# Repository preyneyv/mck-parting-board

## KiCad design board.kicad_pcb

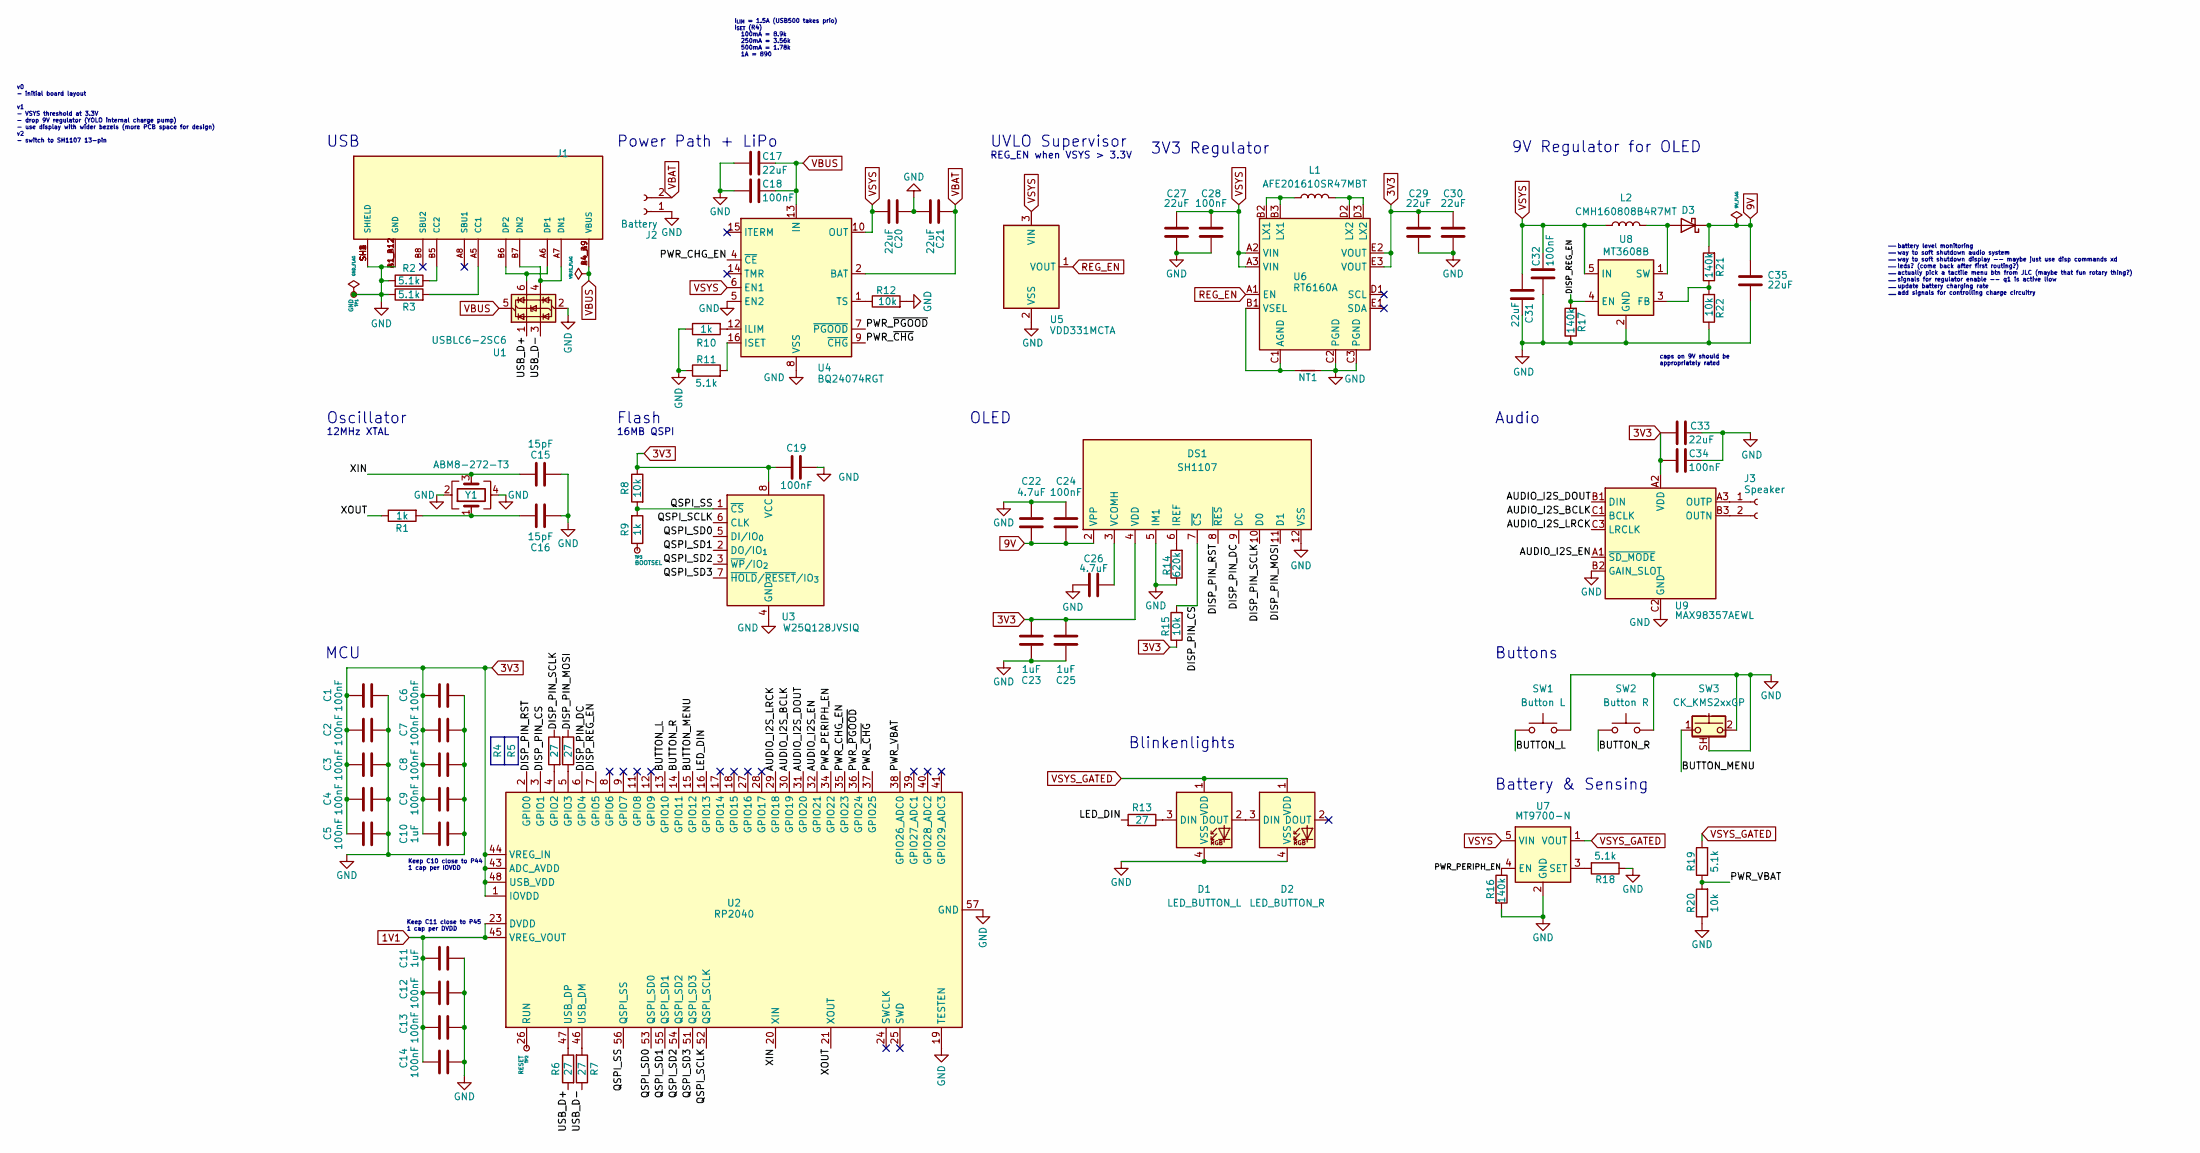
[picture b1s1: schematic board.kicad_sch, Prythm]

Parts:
C1, C2, C3, C4, C5, C6, C7, C8, C9, C12, C13, C14, C18, C19, C24, C28, C32, C34: 100nF; C_0201_0603Metric; LCSC C307380
C10, C11, C23, C25: 1uF; C_0201_0603Metric; LCSC C307385
C15, C16: 15pF; C_0201_0603Metric; LCSC C237567
C17, C20, C21, C27, C29, C30, C31, C33, C35: 22uF; C_0603_1608Metric; LCSC C2762594
C22, C26: 4.7uF; C_0402_1005Metric; LCSC C318563
D1: LED_BUTTON_L; LED_MX_6028R; LCSC C5242955
D2: LED_BUTTON_R; LED_MX_6028R; LCSC C5242955
D3: BAT20JFILM; D_SOD-323; LCSC C155590
DS1: SH1107; OLED_SH1107_13P
J1: UJ20-C-H-G-MSMT-6-P16-TR; SAMESKY_UJ20-C-H-G-MSMT-6-P16-TR; PARTREV 1.0; DigiKey 2223-UJ20-C-H-G-MSMT-6-P16-TRCT-ND
J2: Battery; JST_PH_B2B-PH-K_1x02_P2.00mm_Vertical; DigiKey 455-1704-ND
J3: Speaker; JST_ZH_B2B-ZR_1x02_P1.50mm_Vertical; DigiKey 455-B2B-ZR-ND
L1: AFE201610SR47MBT; L_Murata_DFE201610P; LCSC C22459313
L2: CMH160808B4R7MT; L_0603_1608Metric; LCSC C394952
NT1: NetTie_2; NetTie-2_SMD_Pad0.5mm
R1, R9, R10: 1k; R_0201_0603Metric; LCSC C138165
R2, R3, R11, R18, R19: 5.1k; R_0201_0603Metric; LCSC C274341
R4, R5, R6, R7, R13: 27; R_0201_0603Metric; LCSC C273268
R8, R12, R15, R20, R22: 10k; R_0201_0603Metric; LCSC C138117
R14: 620k; R_0201_0603Metric; LCSC C295860
R16, R17, R21: 140k; R_0201_0603Metric; LCSC C138174
SW1: Button L; SW_Hotswap_Kailh_MX_Plated
SW2: Button R; SW_Hotswap_Kailh_MX_Plated
SW3: CK_KMS2xxGP; SW_SPST_CK_KMS2xxGP; DigiKey 401-1614-1-ND
TP1: GND; TestPoint_Pad_1.0x1.0mm
TP2: RESET; TestPoint_Pad_1.0x1.0mm
TP3: BOOTSEL; TestPoint_Pad_1.0x1.0mm
U1: USBLC6-2SC6; SOT-23-6; LCSC C7519
U2: RP2040; QFN-56-1EP_7x7mm_P0.4mm_EP3.2x3.2mm; LCSC C2040
U3: W25Q128JVSIQ; SOIC-8_5.3x5.3mm_P1.27mm; LCSC C97521
U4: BQ24074RGT; VQFN-16-1EP_3x3mm_P0.5mm_EP1.6x1.6mm; LCSC C54313
U5: VDD331MCTA; SOT-23; LCSC C697886
U6: RT6160A; WL-CSP-15B_1.4x2.3_BSC; LCSC C7065276
U7: MT9700-N; SOT-23-5; LCSC C42441843
U8: MT3608B; SOT-23-6; LCSC C19189893
U9: MAX98357AEWL; WLP-9_3x3_1.437x1.347mm_W91F1+1; LCSC C2682619
Y1: ABM8-272-T3; Crystal_SMD_3225-4Pin_3.2x2.5mm; LCSC C20625731

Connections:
1V1: C11.2, C12.1, C13.1, C14.1, U2.23 (DVDD), U2.45 (VREG_VOUT), U2.50 (DVDD)
3V3: C1.1, C2.1, C3.1, C4.1, C5.1, C6.1, C7.1, C8.1, C9.1, C10.2, C19.1, C23.1, C25.1, C29.1, C30.1, C33.2, C34.1, DS1.4 (VDD), R8.1, R15.1, U2.1 (IOVDD), U2.10 (IOVDD), U2.22 (IOVDD), U2.33 (IOVDD), U2.42 (IOVDD), U2.43 (ADC_AVDD), U2.44 (VREG_IN), U2.48 (USB_VDD), U2.49 (IOVDD), U3.8 (VCC), U6.E2 (VOUT), U6.E3 (VOUT), U9.A2 (VDD)
9V: C22.1, C24.1, C35.1, D3.1 (K), DS1.2 (VPP), R21.2
/AUDIO_I2S_BCLK: U2.30 (GPIO19), U9.C1 (BCLK)
/AUDIO_I2S_DOUT: U2.31 (GPIO20), U9.B1 (DIN)
/AUDIO_I2S_EN: U2.32 (GPIO21), U9.A1 (~SD_MODE)
/AUDIO_I2S_LRCK: U2.29 (GPIO18), U9.C3 (LRCLK)
/BUTTON_L: SW1.1, U2.13 (GPIO10)
/BUTTON_MENU: SW3.1, U2.15 (GPIO12)
/BUTTON_R: SW2.1, U2.14 (GPIO11)
/DISP_PIN_CS: DS1.7 (~CS), R15.2, U2.3 (GPIO1)
/DISP_PIN_DC: DS1.9 (DC), U2.6 (GPIO4)
/DISP_PIN_MOSI: DS1.11 (D1), R5.2
/DISP_PIN_RST: DS1.8 (~RES), U2.2 (GPIO0)
/DISP_PIN_SCLK: DS1.10 (D0), R4.1
/DISP_REG_EN: R17.2, U2.7 (GPIO5), U8.4 (EN)
/LED_DIN: R13.2, U2.16 (GPIO13)
/PWR_CHG_EN: U2.35 (GPIO23), U4.4 (~CE)
/PWR_PERIPH_EN: R16.1, U2.34 (GPIO22), U7.4 (EN)
/PWR_VBAT: R19.1, R20.2, U2.38 (GPIO26_ADC0)
/PWR_~CHG: U2.37 (GPIO25), U4.9 (~CHG)
/PWR_~PGOOD: U2.36 (GPIO24), U4.7 (~PGOOD)
/QSPI_SCLK: U2.52 (QSPI_SCLK), U3.6 (CLK)
/QSPI_SD0: U2.53 (QSPI_SD0), U3.5 (DI/IO_{0})
/QSPI_SD1: U2.55 (QSPI_SD1), U3.2 (DO/IO_{1})
/QSPI_SD2: U2.54 (QSPI_SD2), U3.3 (~WP/IO_{2})
/QSPI_SD3: U2.51 (QSPI_SD3), U3.7 (~HOLD/~RESET/IO_{3})
/QSPI_SS: R8.2, R9.2, U2.56 (QSPI_SS), U3.1 (~CS)
/USB_D+: R6.2, U1.1 (I/O1)
/USB_D-: R7.1, U1.3 (I/O2)
/XIN: C15.1, U2.20 (XIN), Y1.3
/XOUT: R1.1, U2.21 (XOUT)
GND: C1.2, C2.2, C3.2, C4.2, C5.2, C6.2, C7.2, C8.2, C9.2, C10.1, C11.1, C12.2, C13.2, C14.2, C15.2, C16.1, C17.1, C18.1, C19.2, C20.1, C21.2, C22.2, C23.2, C24.2, C25.2, C26.2, C27.2, C28.2, C29.2, C30.2, C31.1, C32.1, C33.1, C34.2, C35.2, D1.4 (VSS), D2.4 (VSS), DS1.5 (IM1), DS1.12 (VSS), J1.A1_B12 (GND), J1.B1_A12 (GND), J1.SH1 (SHIELD), J1.SH2 (SHIELD), J1.SH3 (SHIELD), J1.SH4 (SHIELD), J2.1, NT1.2, R2.2, R3.1, R10.1, R11.1, R12.2, R14.1, R16.2, R17.1, R18.1, R20.1, R22.1, SW1.2, SW2.2, SW3.2, SW3.SH (B), TP1.1, U1.2 (GND), U2.19 (TESTEN), U2.57 (GND), U3.4 (GND), U4.5 (EN2), U4.8 (VSS), U4.17 (VSS), U5.2 (VSS), U6.C2 (PGND), U6.C3 (PGND), U7.2 (GND), U8.2 (GND), U9.B2 (GAIN_SLOT), U9.C2 (GND), Y1.2, Y1.4
unnamed: C16.2, R1.2, Y1.1
unnamed: D1.3 (DIN), R13.1
unnamed: D1.2 (DOUT), D2.3 (DIN)
unnamed: D3.2 (A), L2.2, U8.1 (SW)
unnamed: DS1.6 (IREF), R14.2
unnamed: C26.1, DS1.3 (VCOMH)
unnamed: J1.A5 (CC1), R3.2
unnamed: J1.B5 (CC2), R2.1
unnamed: J1.A7 (DN1), J1.B7 (DN2), U1.4 (I/O2)
unnamed: J1.A6 (DP1), J1.B6 (DP2), U1.6 (I/O1)
unnamed: J3.1, U9.A3 (OUTP)
unnamed: J3.2, U9.B3 (OUTN)
unnamed: L1.1, U6.B2 (LX1), U6.B3 (LX1)
unnamed: L1.2, U6.D2 (LX2), U6.D3 (LX2)
unnamed: R9.1, TP3.1
unnamed: R4.2, U2.4 (GPIO2)
unnamed: R5.1, U2.5 (GPIO3)
unnamed: TP2.1, U2.26 (RUN)
unnamed: R7.2, U2.46 (USB_DM)
unnamed: R6.1, U2.47 (USB_DP)
unnamed: R10.2, U4.12 (ILIM)
unnamed: R11.2, U4.16 (ISET)
unnamed: R12.1, U4.1 (TS)
unnamed: NT1.1, U6.B1 (VSEL), U6.C1 (AGND)
unnamed: R18.2, U7.3 (SET)
unnamed: R21.1, R22.2, U8.3 (FB)
REG_EN: U5.1 (VOUT), U6.A1 (EN)
VBAT: C21.1, J2.2, U4.2 (BAT), U4.3 (BAT)
VBUS: C17.2, C18.2, J1.A4_B9 (VBUS), J1.B4_A9 (VBUS), U1.5 (VBUS), U4.13 (IN)
VSYS: C20.2, C27.1, C28.1, C31.2, C32.2, L2.1, U4.6 (EN1), U4.10 (OUT), U4.11 (OUT), U5.3 (VIN), U6.A2 (VIN), U6.A3 (VIN), U7.5 (VIN), U8.5 (IN)
VSYS_GATED: D1.1 (VDD), D2.1 (VDD), R19.2, U7.1 (VOUT)

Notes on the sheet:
battery level monitoring way to soft shutdown audio system way to soft shutdown display -- maybe just use disp commands xd leds? (come back after first routing?) actually pick a tactile menu btn from JLC (maybe that fun rotary thing?) signals for regulator enable -- q1 is active llow update battery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
9V Regulator for OLED
Buttons
Oscillator
Blinkenlights
3V3 Regulator
Keep C10 close to P44 1 cap per IOVDD
12MHz XTAL
USB
16MB QSPI
I_{LIM} = 1.5A (USB500 takes prio) I_{SET} (R4) 100mA = 8.9k 250mA = 3.56k 500mA = 1.78k 1A = 890
UVLO Supervisor
Audio
Battery & Sensing
Flash
Power Path + LiPo
REG_EN when VSYS > 3.3V
MCU
OLED
Keep C11 close to P45 1 cap per DVDD
caps on 9V should be appropriately rated
v0 - initial board layout v1 - VSYS threshold at 3.3V - drop 9V regulator (YOLO internal charge pump) - use display with wider bezels (more PCB space for design) v2 - switch to SH1107 13-pin

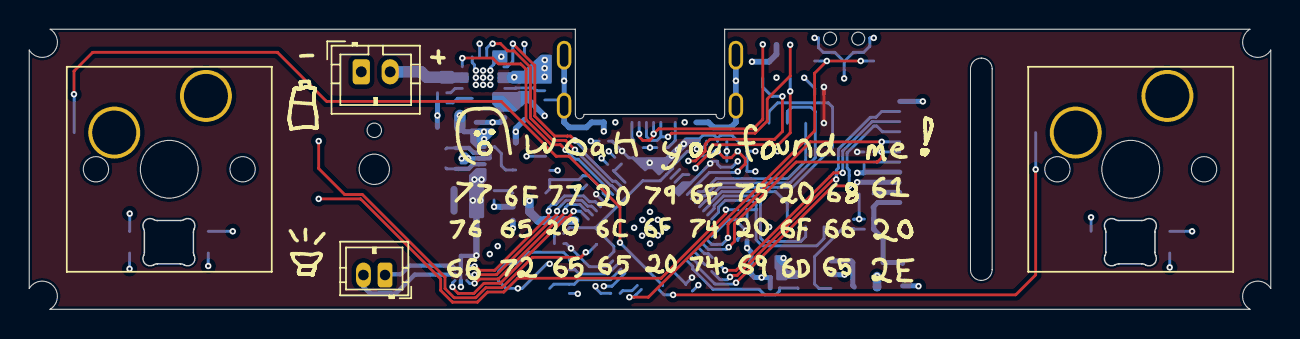
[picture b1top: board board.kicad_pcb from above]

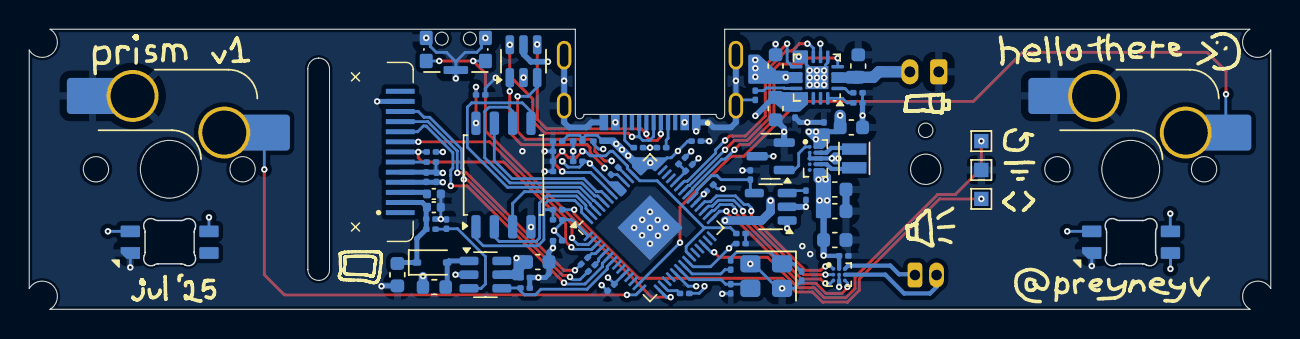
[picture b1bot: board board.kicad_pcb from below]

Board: 4 copper layers, 86.0 x 19.4 mm, 83 parts (79 on the bottom side), 64 nets.

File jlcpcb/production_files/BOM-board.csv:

Comment,Designator,Footprint,LCSC,Quantity
10k,"R12,R15,R20,R22,R8",R_0201_0603Metric,C138117,5
1k,"R1,R10,R9",R_0201_0603Metric,C138165,3
140k,"R16,R17,R21",R_0201_0603Metric,C138174,3
BAT20JFILM,D3,D_SOD-323,C155590,1
MT3608B,U8,SOT-23-6,C19189893,1
RP2040,U2,QFN-56-1EP_7x7mm_P0.4mm_EP3.2x3.2mm,C2040,1
ABM8-272-T3,Y1,Crystal_SMD_3225-4Pin_3.2x2.5mm,C20625731,1
AFE201610SR47MBT,L1,L_Murata_DFE201610P,C22459313,1
15pF,"C15,C16",C_0201_0603Metric,C237567,2
MAX98357AEWL,U9,WLP-9_3x3_1.437x1.347mm_W91F1+1,C2682619,1
27,"R13,R4,R5,R6,R7",R_0201_0603Metric,C273268,5
5.1k,"R11,R18,R19,R2,R3",R_0201_0603Metric,C274341,5
22uF,"C17,C20,C21,C27,C29,C30,C31,C33,C35",C_0603_1608Metric,C2762594,9
620k,R14,R_0201_0603Metric,C295860,1
100nF,"C1,C12,C13,C14,C18,C19,C2,C24,C28,C3,C32,C34,C4,C5,C6,C7,C8,C9",C_0201_0603Metric,C307380,18
1uF,"C10,C11,C23,C25",C_0201_0603Metric,C307385,4
4.7uF,"C22,C26",C_0402_1005Metric,C318563,2
CMH160808B4R7MT,L2,L_0603_1608Metric,C394952,1
MT9700-N,U7,SOT-23-5,C42441843,1
LED_BUTTON_L,"D1,D2",LED_MX_6028R,C5242955,2
BQ24074RGT,U4,VQFN-16-1EP_3x3mm_P0.5mm_EP1.6x1.6mm,C54313,1
VDD331MCTA,U5,SOT-23,C697886,1
RT6160A,U6,WL-CSP-15B_1.4x2.3_BSC,C7065276,1
USBLC6-2SC6,U1,SOT-23-6,C7519,1
W25Q128JVSIQ,U3,SOIC-8_5.3x5.3mm_P1.27mm,C97521,1

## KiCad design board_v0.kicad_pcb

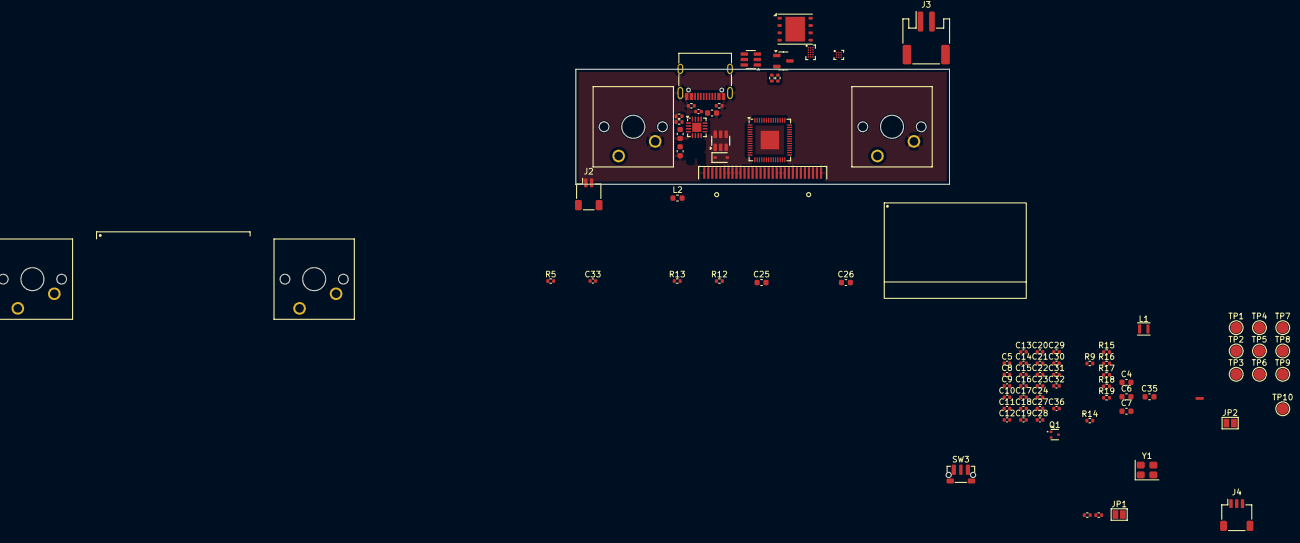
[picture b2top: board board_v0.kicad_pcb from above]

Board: 4 copper layers, 65.0 x 20.0 mm, 92 parts (0 on the bottom side), 59 nets.

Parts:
C1, C3, C4, C6, C7, C25, C26, C34, C35: 22uF; C_0603_1608Metric
C2, C5, C8, C9, C10, C11, C12, C13, C14, C15, C16, C19, C20, C21, C22, C29, C31, C33, C36: 100nF; C_0402_1005Metric
C17, C18, C30, C32: 1uF; C_0402_1005Metric
C23, C24: 15pF; C_0402_1005Metric
C27, C28: 4.7uF; C_0402_1005Metric
D1: BAT20JFILM; D_SOD-323
DS1: X096-2864KSWPG01-H30; OLED-128O064D
Display: OLED 128x64 0.96"; OLED_128x64_0.96in
Display#2: OLED 128x64 0.96"; OLED_128x64_0.96in
J1: USB_C_Receptacle_USB2.0_14P; USB_C_Receptacle_G-Switch_GT-USB-7010ASV
J2: Battery; JST_SH_SM02B-SRSS-TB_1x02-1MP_P1.00mm_Horizontal
J3: Speaker; JST_PH_S2B-PH-SM4-TB_1x02-1MP_P2.00mm_Horizontal
J4: SWD; JST_SH_SM03B-SRSS-TB_1x03-1MP_P1.00mm_Horizontal
JP1: BOOTSEL; SolderJumper-2_P1.3mm_Open_Pad1.0x1.5mm
JP2: RESET; SolderJumper-2_P1.3mm_Open_Pad1.0x1.5mm
L1: 0.47uH; L_Murata_DFE201610P
L2: 4.7uH; L_0603_1608Metric
NT1: NetTie_2; NetTie-2_SMD_Pad0.5mm
Q1: DMG1012T; SOT-523
R1, R2: 5.1k; R_0402_1005Metric
R3, R7, R13, R17, R19: 10k; R_0402_1005Metric
R4, R18: 3.6k; R_0402_1005Metric
R5, R12: 140k; R_0402_1005Metric
R8, R9: 1k; R_0402_1005Metric
R10, R11, R15, R16: 27; R_0402_1005Metric
R14: 620k; R_0402_1005Metric
SW1, SW1#2: Button L; SW_Cherry_MX_1.00u_PCB
SW2, SW2#2: Button R; SW_Cherry_MX_1.00u_PCB
SW3: Menu; SW_Push_1P1T-MP_NO_Horizontal_Alps_SKRTLAE010
TP1: GND; TestPoint_Pad_D2.0mm
TP2: VBUS; TestPoint_Pad_D2.0mm
TP3: VSYS; TestPoint_Pad_D2.0mm
TP4: VBAT; TestPoint_Pad_D2.0mm
TP5: 3V3; TestPoint_Pad_D2.0mm
TP6: 9V; TestPoint_Pad_D2.0mm
TP7: REG_EN; TestPoint_Pad_D2.0mm
TP8: SNS_VBAT; TestPoint_Pad_D2.0mm
TP9: SNS_~{CHG}; TestPoint_Pad_D2.0mm
TP10: SNS_~{PGOOD}; TestPoint_Pad_D2.0mm
U1: RP2040; QFN-56-1EP_7x7mm_P0.4mm_EP3.2x3.2mm
U2: BQ24074RGT; VQFN-16-1EP_3x3mm_P0.5mm_EP1.6x1.6mm
U3: RT6160A; WL-CSP-15B_1.4x2.3_BSC
U4: TLV809EF30DBZR; SOT-23-3
U5: W25Q128JVPIQ; WSON-8-1EP_6x5mm_P1.27mm_EP3.4x4.3mm
U6: USBLC6-2SC6; SOT-23-6
U7: MT3608B; SOT-23-6
U8: MAX98357AEWL; WLP-9_3x3_1.437x1.347mm_W91F1+1
Y1: ABM8-272-T3; Crystal_SMD_3225-4Pin_3.2x2.5mm

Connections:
1V1: C18.2, C19.1, C20.1, C21.1, U1.23 (DVDD), U1.45 (VREG_VOUT), U1.50 (DVDD)
3V3: C6.1, C7.1, C8.1, C9.1, C10.1, C11.1, C12.1, C13.1, C14.1, C15.1, C16.1, C17.2, C22.1, C29.1, C30.1, C32.1, C35.2, C36.1, DS1.6 (VBAT), DS1.9 (VDD), Q1.1 (G), R7.1, R17.1, TP5.1, U1.1 (IOVDD), U1.10 (IOVDD), U1.22 (IOVDD), U1.33 (IOVDD), U1.42 (IOVDD), U1.43 (ADC_AVDD), U1.44 (VREG_IN), U1.48 (USB_VDD), U1.49 (IOVDD), U3.E2 (VOUT), U3.E3 (VOUT), U5.8 (VCC), U8.A2 (VDD)
9V: C26.1, C28.1, C31.1, D1.1 (K), DS1.28 (VCC), R12.2, TP6.1
/AUDIO_I2S_BCLK: U1.9 (GPIO7), U8.C1 (BCLK)
/AUDIO_I2S_DOUT: U1.8 (GPIO6), U8.B1 (DIN)
/AUDIO_I2S_LRCK: U1.11 (GPIO8), U8.C3 (LRCLK)
/AUDIO_I2S_SD: U1.12 (GPIO9), U8.A1 (~SD_MODE)
/BUTTON_L: SW1#2.1, U1.13 (GPIO10)
/BUTTON_MENU: SW3.1, U1.15 (GPIO12)
/BUTTON_R: SW2#2.1, U1.14 (GPIO11)
/DISP_PIN_CS: DS1.13 (~CS), R17.2, U1.3 (GPIO1)
/DISP_PIN_DC: DS1.15 (D/~C), U1.6 (GPIO4)
/DISP_PIN_MOSI: DS1.19 (D1), R16.2
/DISP_PIN_RST: DS1.14 (~RES), U1.2 (GPIO0)
/DISP_PIN_SCLK: DS1.18 (D0), R15.1
/DISP_PIN_VCC: R5.2, U1.7 (GPIO5), U7.4 (EN)
/QSPI_SCLK: U1.52 (QSPI_SCLK), U5.6 (CLK)
/QSPI_SD0: U1.53 (QSPI_SD0), U5.5 (DI/IO_{0})
/QSPI_SD1: U1.55 (QSPI_SD1), U5.2 (DO/IO_{1})
/QSPI_SD2: U1.54 (QSPI_SD2), U5.3 (~WP/IO_{2})
/QSPI_SD3: U1.51 (QSPI_SD3), U5.7 (~HOLD/~RESET/IO_{3})
/QSPI_SS: R7.2, R8.2, U1.56 (QSPI_SS), U5.1 (~CS)
/SNS_VBAT: Q1.3 (D), TP8.1, U1.38 (GPIO26_ADC0)
/SNS_~CHG: TP9.1, U1.37 (GPIO25), U2.9 (~CHG)
/SNS_~PGOOD: TP10.1, U1.36 (GPIO24), U2.7 (~PGOOD)
/USB_DM: R11.1, U6.3 (I/O2)
/USB_DP: R10.2, U6.1 (I/O1)
/XIN: C23.1, U1.20 (XIN), Y1.3
/XOUT: R9.1, U1.21 (XOUT)
GND: C1.2, C2.1, C3.1, C4.2, C5.2, C6.2, C7.2, C8.2, C9.2, C10.2, C11.2, C12.2, C13.2, C14.2, C15.2, C16.2, C17.1, C18.1, C19.2, C20.2, C21.2, C22.2, C23.2, C24.1, C25.1, C26.2, C27.2, C28.2, C29.2, C30.2, C31.2, C32.2, C33.1, C34.1, C35.1, C36.2, DS1.1 (GND), DS1.8 (VSS), DS1.10 (BS0), DS1.11 (BS1), DS1.12 (BS2), DS1.16 (R/~W), DS1.17 (E/~RD), DS1.21 (D3), DS1.22 (D4), DS1.23 (D5), DS1.24 (D6), DS1.25 (D7), DS1.29 (VLSS), DS1.30 (GND), J1.A1 (GND), J1.A12 (GND), J1.B1 (GND), J1.B12 (GND), J1.S1 (SHIELD), J2.2, J4.2, JP1.1 (A), JP2.1 (A), NT1.2, R1.1, R2.2, R3.2, R4.1, R5.1, R13.1, R14.1, R18.1, SW1#2.2, SW2#2.2, SW3.2, TP1.1, U1.19 (TESTEN), U1.57 (GND), U2.4 (~CE), U2.5 (EN2), U2.8 (VSS), U2.17 (VSS), U3.B1 (VSEL), U3.C2 (PGND), U3.C3 (PGND), U4.1 (GND), U5.4 (GND), U6.2 (GND), U7.2 (GND), U8.B2 (GAIN_SLOT), U8.C2 (GND), Y1.2, Y1.4
unnamed: C24.2, R9.2, Y1.1
unnamed: D1.2 (A), L2.2, U7.1 (SW)
unnamed: DS1.26 (IREF), R14.2
unnamed: C27.1, DS1.27 (VCOMH)
unnamed: J1.A5 (CC1), R1.2
unnamed: J1.B5 (CC2), R2.1
unnamed: J1.A6 (D+), J1.B6 (D+), U6.6 (I/O1)
unnamed: J1.A7 (D-), J1.B7 (D-), U6.4 (I/O2)
unnamed: J3.1, U8.A3 (OUTP)
unnamed: J3.2, U8.B3 (OUTN)
unnamed: J4.1, U1.24 (SWCLK)
unnamed: J4.3, U1.25 (SWD)
unnamed: JP1.2 (B), R8.1
unnamed: JP2.2 (B), U1.26 (RUN)
unnamed: L1.1, U3.B2 (LX1), U3.B3 (LX1)
unnamed: L1.2, U3.D2 (LX2), U3.D3 (LX2)
unnamed: Q1.2 (S), R18.2, R19.1
unnamed: R15.2, U1.4 (GPIO2)
unnamed: R16.1, U1.5 (GPIO3)
unnamed: R11.2, U1.46 (USB_DM)
unnamed: R10.1, U1.47 (USB_DP)
unnamed: R4.2, U2.16 (ISET)
unnamed: R3.1, U2.1 (TS)
unnamed: NT1.1, U3.C1 (AGND), U3.D1 (SCL), U3.E1 (SDA)
unnamed: R12.1, R13.2, U7.3 (FB)
REG_EN: TP7.1, U3.A1 (EN), U4.2 (~RESET)
VBAT: C1.1, J2.1, R19.2, TP4.1, U2.2 (BAT), U2.3 (BAT)
VBUS: C2.2, C34.2, J1.A4 (VBUS), J1.A9 (VBUS), J1.B4 (VBUS), J1.B9 (VBUS), TP2.1, U2.13 (IN), U6.5 (VBUS)
VSYS: C3.2, C4.1, C5.1, C25.2, C33.2, L2.1, TP3.1, U2.6 (EN1), U2.10 (OUT), U2.11 (OUT), U3.A2 (VIN), U3.A3 (VIN), U4.3 (VCC), U7.5 (IN)

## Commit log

2025-07-17 'yay'
2025-07-18 routing complete??
2025-07-19 done (?)
2025-07-19 ordered
